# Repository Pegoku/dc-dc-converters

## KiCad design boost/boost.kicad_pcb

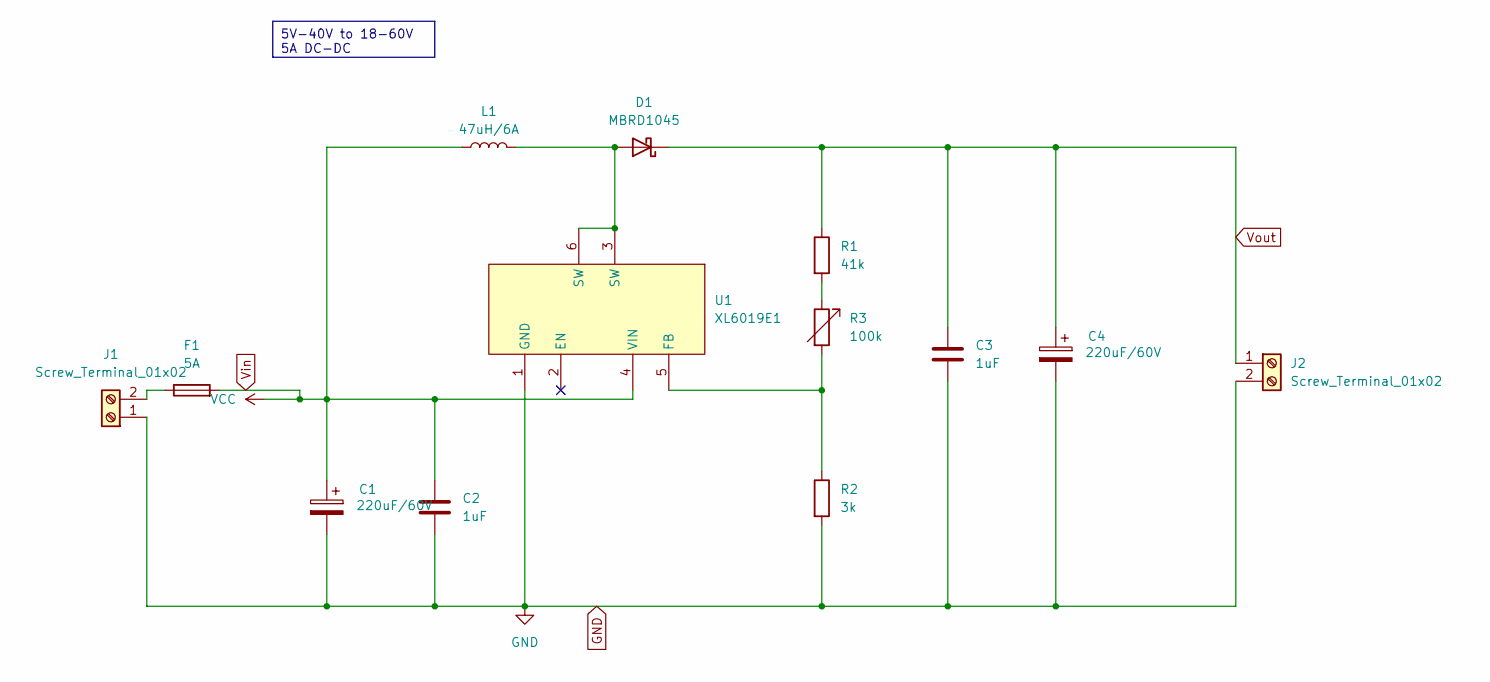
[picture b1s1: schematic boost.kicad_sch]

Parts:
C1, C4: 220uF/60V; CP_Elec_10x10.5
C2, C3: 1uF; C_1206_3216Metric
D1: MBRD1045; TO-252-2; LCSC C5137764
F1: 5A; Fuse_1206_3216Metric; LCSC C553937
J1, J2: Screw_Terminal_01x02; TerminalBlock_Phoenix_MKDS-1,5-2-5.08_1x02_P5.08mm_Horizont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
L1: 47uH/6A; C_Rect_L26.5mm_W11.5mm_P22.50mm_MKS4; LCSC C18213939
R1: 41k; R_1206_3216Metric
R2: 3k; R_1206_3216Metric
R3: 100k; Potentiometer_Bourns_3266Y_Vertical
U1: XL6019E1; TO-263-5_L10.2-W9.9-P1.70-LS14.4-TL; LCSC Part C73018

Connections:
GND: C1.2, C2.2, C3.2, C4.2, J1.1, J2.2, R2.2, U1.1 (GND)
unnamed: D1.2 (A), L1.2, U1.3 (SW), U1.6 (SW)
unnamed: F1.1, J1.2
unnamed: R1.2, R3.1
unnamed: R2.1, R3.2, U1.5 (FB)
Vin: C1.1, C2.1, F1.2, L1.1, U1.4 (VIN)
Vout: C3.1, C4.1, D1.1 (K), J2.1, R1.1

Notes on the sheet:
5V-40V to 18-60V 5A DC-DC

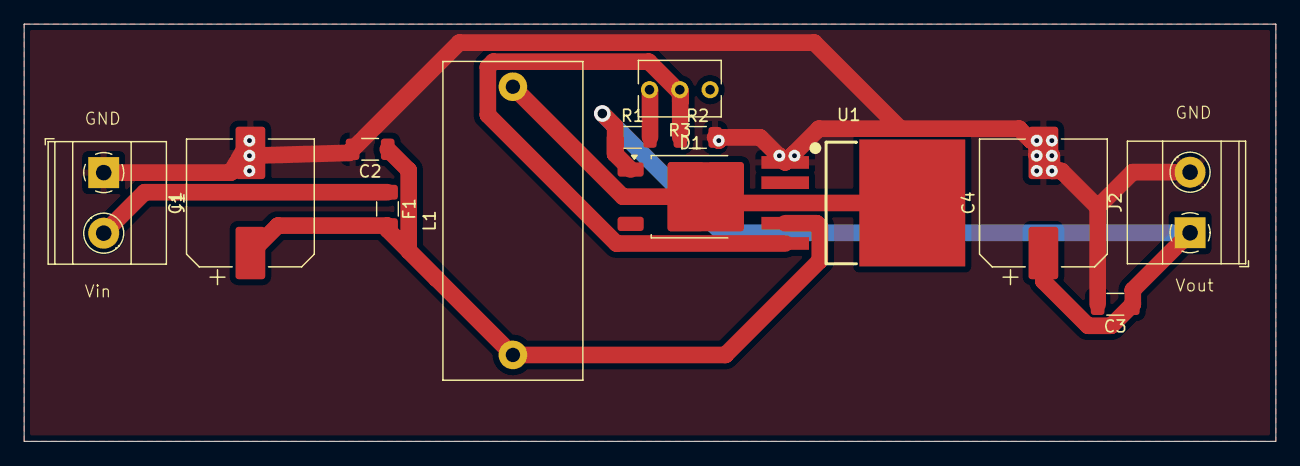
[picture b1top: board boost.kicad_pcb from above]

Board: 2 copper layers, 105.0 x 35.0 mm, 13 parts (0 on the bottom side), 7 nets.

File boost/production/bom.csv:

Designator,Footprint,Quantity,Value,LCSC Part #
"C1, C4",CP_Elec_10x10.5,2,220uF/60V,
"C2, C3",1206,2,1uF,
D1,TO-252-2,1,MBRD1045,C5137764
F1,1206,1,5A,C553937
"J1, J2","TerminalBlock_Phoenix_MKDS-1,5-2-5.08_1x02_P5.08mm_Horizontal",2,Screw_Terminal_01x02,
L1,C_Rect_L26.5mm_W11.5mm_P22.50mm_MKS4,1,47uH/6A,C18213939
R1,1206,1,41k,
R2,1206,1,3k,
R3,Potentiometer_Bourns_3266Y_Vertical,1,100k,
U1,TO-263-5_L10.2-W9.9-P1.70-LS14.4-TL,1,XL6019E1,C73018

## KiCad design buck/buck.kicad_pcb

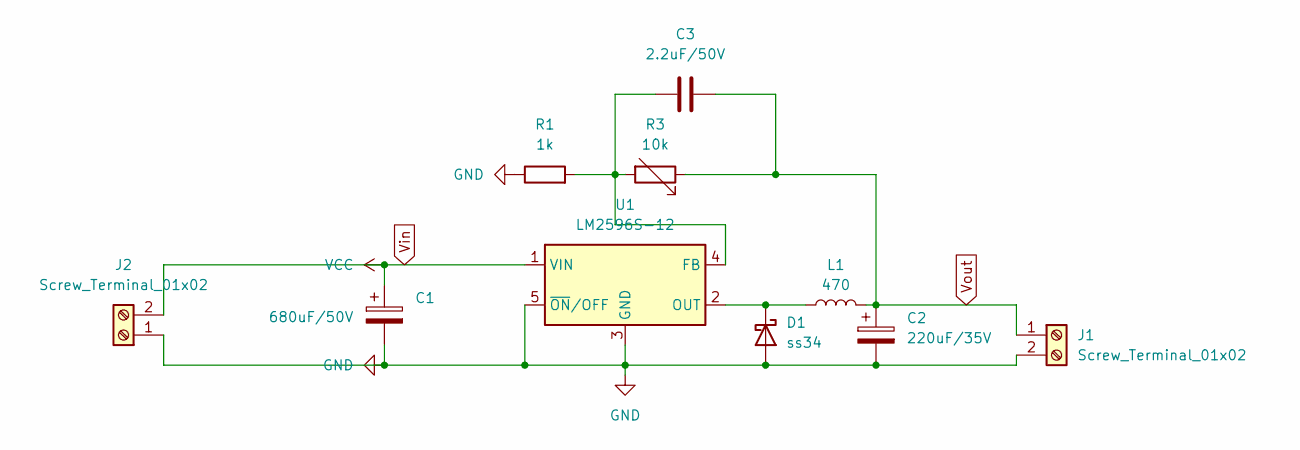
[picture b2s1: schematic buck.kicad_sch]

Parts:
C1: 680uF/50V; CP_Elec_10x12.5
C2: 220uF/35V; C_Elec_8x10.2
C3: 2.2uF/50V; C_0201_0603Metric
D1: ss34; D_SMA
J1, J2: Screw_Terminal_01x02; TerminalBlock_Phoenix_MKDS-1,5-2-5.08_1x02_P5.08mm_Horizont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
L1: 470; L_SXN_SMDRI127
R1: 1k; R_1206_3216Metric
R3: 10k; Potentiometer_Bourns_3296W_Vertical
U1: LM2596S-12; TO-263-5_TabPin3

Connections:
GND: C1.2, C2.2, D1.2 (A), J1.2, J2.1, R1.1, U1.3 (GND), U1.5 (~ON/OFF)
unnamed: D1.1 (K), L1.1, U1.2 (OUT)
unnamed: C3.1, R1.2, R3.2, U1.4 (FB)
Vin: C1.1, J2.2, U1.1 (VIN)
Vout: C2.1, C3.2, J1.1, L1.2, R3.1

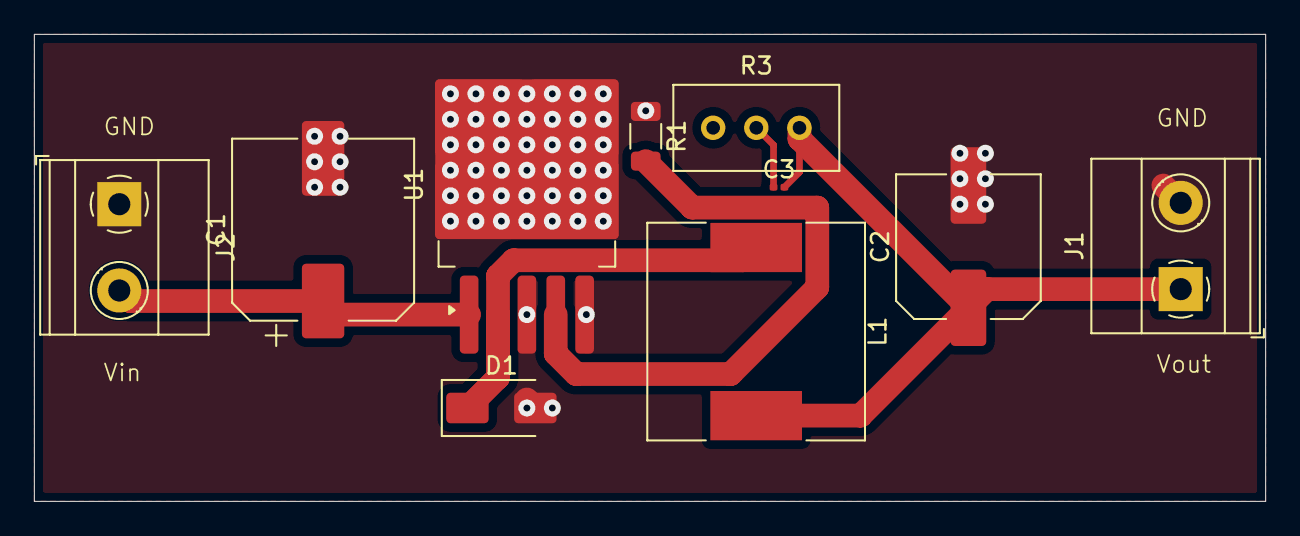
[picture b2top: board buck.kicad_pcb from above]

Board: 2 copper layers, 72.5 x 27.5 mm, 10 parts (0 on the bottom side), 5 nets.

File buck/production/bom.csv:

Designator,Footprint,Quantity,Value,LCSC Part #
C1,CP_Elec_10x12.5,1,680uF/50V,
C2,C_Elec_8x10.2,1,220uF/35V,
C3,0201,1,2.2uF/50V,
D1,D_SMA,1,ss34,
"J1, J2","TerminalBlock_Phoenix_MKDS-1,5-2-5.08_1x02_P5.08mm_Horizontal",2,Screw_Terminal_01x02,
L1,L_SXN_SMDRI127,1,470,
R1,1206,1,1k,
R3,Potentiometer_Bourns_3296W_Vertical,1,10k,
U1,TO-263-5_TabPin3,1,LM2596S-12,

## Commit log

2024-08-18 start
2024-08-20 finish
2024-08-20 finish boost
2024-08-21 buck
2024-08-21 finish 2
